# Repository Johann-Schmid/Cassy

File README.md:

# Cassy
 PCB of the Cassy Interface with the MAX4659

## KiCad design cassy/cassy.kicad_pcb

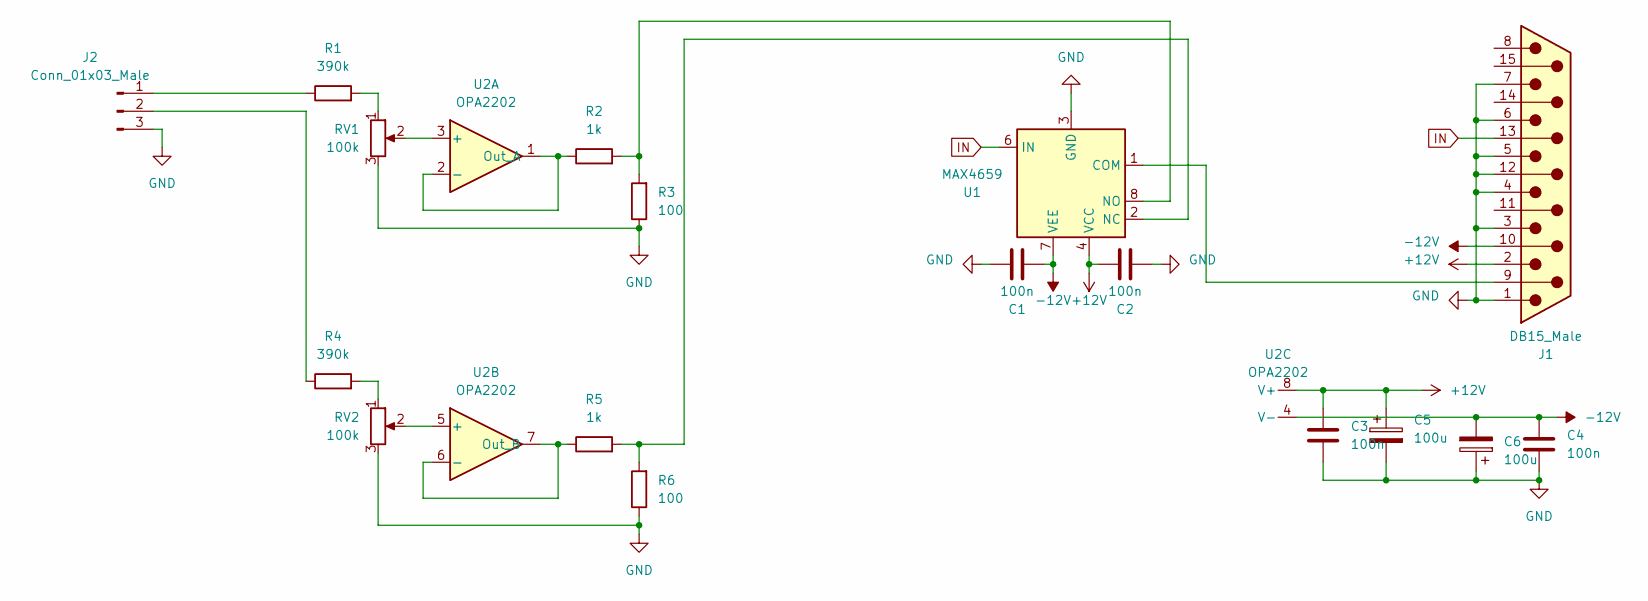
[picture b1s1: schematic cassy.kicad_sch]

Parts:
C1, C2, C3, C4: 100n; C_0805_2012Metric
C5, C6: 100u; CP_Radial_D6.3mm_P2.50mm
J1: DB15_Male; DSUB-15_Male_Horizontal_P2.77x2.84mm_EdgePinOffset9.90mm_Ho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
J2: Conn_01x03_Male; PinHeader_1x03_P2.54mm_Vertical
R1, R4: 390k; R_0805_2012Metric_Pad1.20x1.40mm_HandSolder
R2, R5: 1k; R_0805_2012Metric_Pad1.20x1.40mm_HandSolder
R3, R6: 100; R_0805_2012Metric_Pad1.20x1.40mm_HandSolder
RV1, RV2: 100k; Potentiometer_ACP_CA9-H2,5_Horizontal
U1: MAX4659; SOIC-8_3.9x4.9mm_P1.27mm
U2: OPA2202; MSOP-8_3x3mm_P0.65mm

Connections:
+12V: C2.2, C3.1, C5.1, J1.2, U1.4 (VCC), U2.8 (V+)
-12V: C1.1, C4.1, C6.2, J1.10, U1.7 (VEE), U2.4 (V-)
GND: C1.2, C2.1, C3.2, C4.2, C5.2, C6.1, J1.1, J1.3, J1.4, J1.5, J1.6, J1.7, J1.12, J2.3, R3.1, R6.1, RV1.3, RV2.3, U1.3 (GND)
IN: J1.13, U1.6 (IN)
unnamed: J1.9, U1.1 (COM)
unnamed: J2.1, R1.1
unnamed: J2.2, R4.1
unnamed: R1.2, RV1.1
unnamed: R4.2, RV2.1
unnamed: R5.2, R6.2, U1.2 (NC)
unnamed: R2.2, R3.2, U1.8 (NO)
unnamed: RV1.2, U2.3 (+)
unnamed: R2.1, U2.1 (Out_A), U2.2 (-)
unnamed: RV2.2, U2.5 (+)
unnamed: R5.1, U2.6 (-), U2.7 (Out_B)

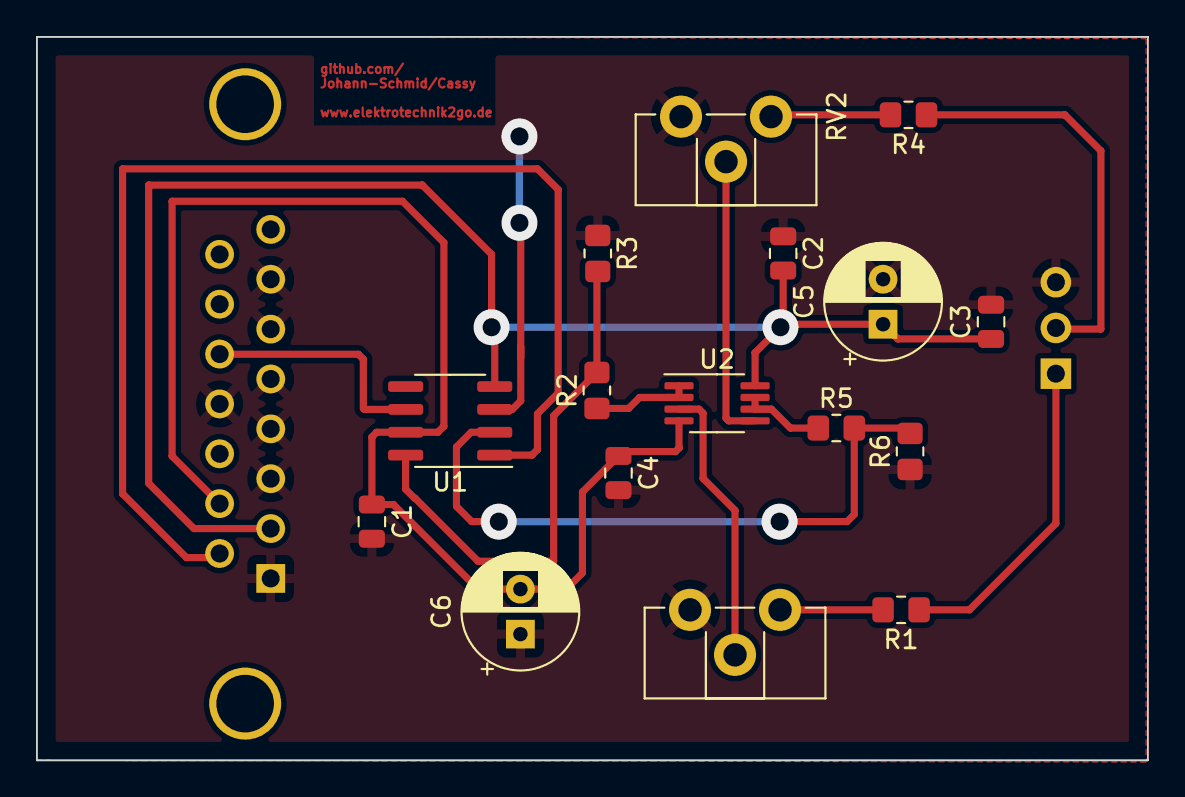
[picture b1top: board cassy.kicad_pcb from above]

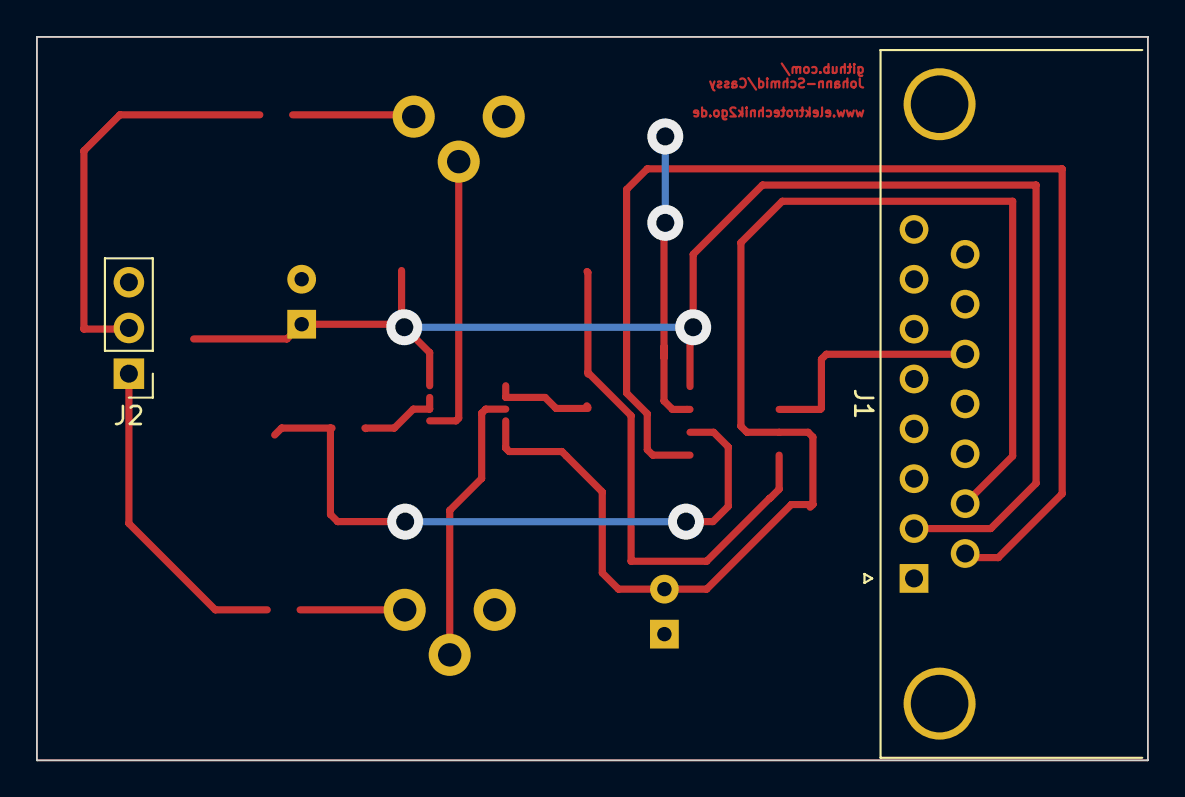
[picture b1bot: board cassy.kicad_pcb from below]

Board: 2 copper layers, 61.7 x 40.2 mm, 18 parts (2 on the bottom side), 15 nets.

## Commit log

2023-06-01 change layer
2023-06-02 insert pdf layout
2023-06-05 insert PDF
2023-06-15 insert pic of pcb
2024-01-11 insert op2202
2024-02-13 update Cassy
2024-03-28 update PCB
    update
